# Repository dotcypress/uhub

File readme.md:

## μHub

### What is it?

μHub is USB Hub Expansion Card designed for [Clockwork uConsole](https://www.clockworkpi.com/uconsole).

### Features

* Internal Speakers Support
* 3 Type-C (USB 2.0) ports with power switch and overcurrent protection
* 1 Internal FFC (USB 2.0) port with power switch and overcurrent protection

## Resources

- [Cover Bracket 3D model](docs/cover.stl)
- [Schematics](docs/uhub.pdf)
- [PCB Viewer](https://kicanvas.org/?github=https%3A%2F%2Fgithub.com%2Fdotcypress%2Fuhub%2Fblob%2Fmain%2Fuhub.kicad_pcb)
- [Interactive BOM](https://htmlpreview.github.io/?https://github.com/dotcypress/uhub/blob/main/docs/ibom.html)

## License

Licensed under either of

- Apache License, Version 2.0 ([LICENSE-APACHE](LICENSE-APACHE) or
  http://www.apache.org/licenses/LICENSE-2.0)
- MIT license ([LICENSE-MIT](LICENSE-MIT) or http://opensource.org/licenses/MIT)

at your option.

### Contribution

Unless you explicitly state otherwise, any contribution intentionally submitted
for inclusion in the work by you, as defined in the Apache-2.0 license, shall be
dual licensed as above, without any additional terms or conditions.

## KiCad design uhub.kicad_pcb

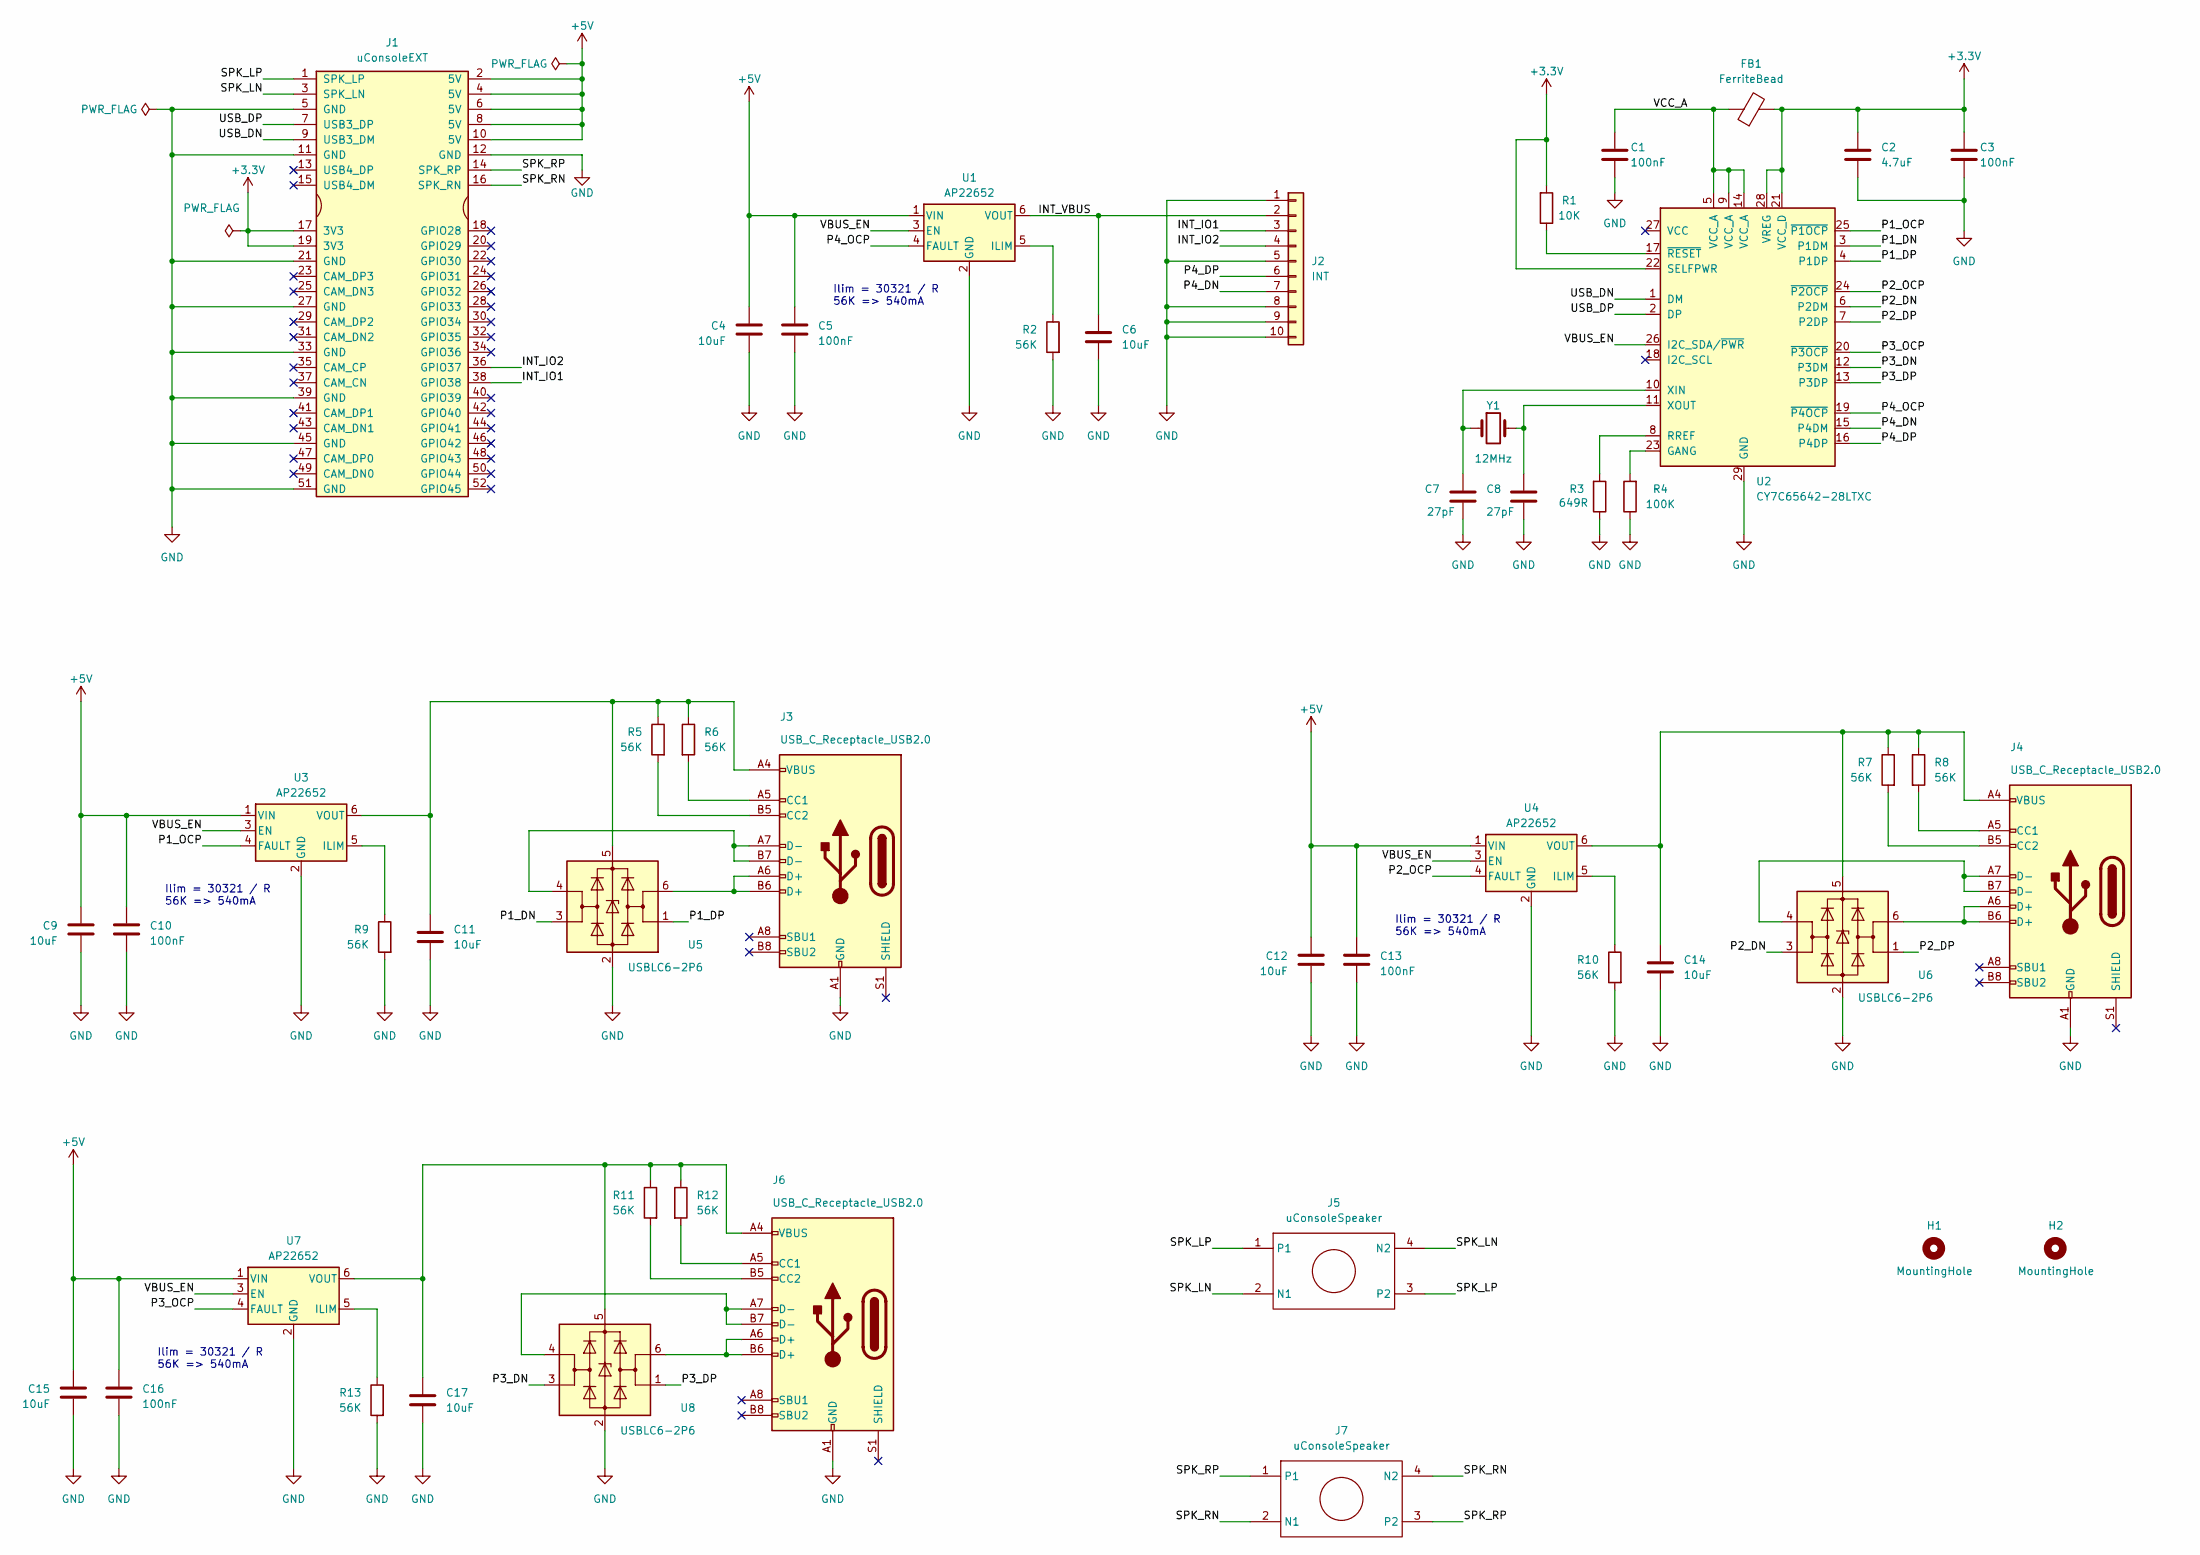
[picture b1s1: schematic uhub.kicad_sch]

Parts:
C1, C3, C5, C10, C13, C16: 100nF; C_0402_1005Metric
C2: 4.7uF; C_0402_1005Metric
C4, C6, C9, C11, C12, C14, C15, C17: 10uF; C_0603_1608Metric
C7, C8: 27pF; C_0402_1005Metric
FB1: FerriteBead; R_0603_1608Metric
H1, H2: MountingHole; MountingHole_5.3mm_M5
J1: uConsoleEXT; ext
J2: INT; Hirose_FH12-10S-0.5SH_1x10-1MP_P0.50mm_Horizontal
J3, J4, J6: USB_C_Receptacle_USB2.0; USB_C_Receptacle_HRO_TYPE-C-31-M-12
J5, J7: uConsoleSpeaker; speaker
R1: 10K; R_0402_1005Metric
R2, R5, R6, R7, R8, R9, R10, R11, R12, R13: 56K; R_0402_1005Metric
R3: 649R; R_0402_1005Metric
R4: 100K; R_0402_1005Metric
U1, U3, U4, U7: AP22652; SOT-23-6
U2: CY7C65642-28LTXC; QFN-28-1EP_5x5mm_P0.5mm_EP3.35x3.35mm
U5, U6, U8: USBLC6-2P6; SOT-666
Y1: 12MHz; Crystal_SMD_5032-2Pin_5.0x3.2mm

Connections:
+3.3V: C2.1, C3.1, FB1.2, J1.17 (3V3), J1.19 (3V3), R1.2, U2.21 (VCC_D), U2.22 (SELFPWR), U2.28 (VREG)
+5V: C4.2, C5.2, C9.2, C10.2, C12.2, C13.2, C15.2, C16.2, J1.2 (5V), J1.4 (5V), J1.6 (5V), J1.8 (5V), J1.10 (5V), U1.1 (VIN), U3.1 (VIN), U4.1 (VIN), U7.1 (VIN)
/INT_IO1: J1.38 (GPIO38), J2.3
/INT_IO2: J1.36 (GPIO37), J2.4
/INT_VBUS: C6.1, J2.2, U1.6 (VOUT)
/P1_DN: U2.3 (P1DM), U5.3 (I/O2)
/P1_DP: U2.4 (P1DP), U5.1 (I/O1)
/P1_OCP: U2.25 (~P1OCP), U3.4 (FAULT)
/P2_DN: U2.6 (P2DM), U6.3 (I/O2)
/P2_DP: U2.7 (P2DP), U6.1 (I/O1)
/P2_OCP: U2.24 (~P2OCP), U4.4 (FAULT)
/P3_DN: U2.12 (P3DM), U8.3 (I/O2)
/P3_DP: U2.13 (P3DP), U8.1 (I/O1)
/P3_OCP: U2.20 (~P3OCP), U7.4 (FAULT)
/P4_DN: J2.7, U2.15 (P4DM)
/P4_DP: J2.6, U2.16 (P4DP)
/P4_OCP: U1.4 (FAULT), U2.19 (~P4OCP)
/SPK_LN: J1.3 (SPK_LN), J5.2 (N1), J5.4 (N2)
/SPK_LP: J1.1 (SPK_LP), J5.1, J5.3 (P2)
/SPK_RN: J1.16 (SPK_RN), J7.2 (N1), J7.4 (N2)
/SPK_RP: J1.14 (SPK_RP), J7.1, J7.3 (P2)
/USB_DN: J1.9 (USB3_DM), U2.1 (DM)
/USB_DP: J1.7 (USB3_DP), U2.2 (DP)
/VBUS_EN: U1.3 (EN), U2.26 (I2C_SDA/~PWR), U3.3 (EN), U4.3 (EN), U7.3 (EN)
/VCC_A: C1.1, FB1.1, U2.5 (VCC_A), U2.9 (VCC_A), U2.14 (VCC_A)
GND: C1.2, C2.2, C3.2, C4.1, C5.1, C6.2, C7.2, C8.2, C9.1, C10.1, C11.2, C12.1, C13.1, C14.2, C15.1, C16.1, C17.2, J1.5 (GND), J1.11 (GND), J1.12 (GND), J1.21 (GND), J1.27 (GND), J1.33 (GND), J1.39 (GND), J1.45 (GND), J1.51 (GND), J2.1, J2.5, J2.8, J2.9, J2.10, J3.A1 (GND), J3.A12 (GND), J3.B1 (GND), J3.B12 (GND), J4.A1 (GND), J4.A12 (GND), J4.B1 (GND), J4.B12 (GND), J6.A1 (GND), J6.A12 (GND), J6.B1 (GND), J6.B12 (GND), R2.2, R3.1, R4.1, R9.2, R10.2, R13.2, U1.2 (GND), U2.29 (GND), U3.2 (GND), U4.2 (GND), U5.2 (GND), U6.2 (GND), U7.2 (GND), U8.2 (GND)
unnamed: J3.A5 (CC1), R6.2
unnamed: J3.B5 (CC2), R5.2
unnamed: J3.A6 (D+), J3.B6 (D+), U5.6 (I/O1)
unnamed: J3.A7 (D-), J3.B7 (D-), U5.4 (I/O2)
unnamed: J4.A5 (CC1), R8.2
unnamed: J4.B5 (CC2), R7.2
unnamed: J4.A6 (D+), J4.B6 (D+), U6.6 (I/O1)
unnamed: J4.A7 (D-), J4.B7 (D-), U6.4 (I/O2)
unnamed: J6.A5 (CC1), R12.2
unnamed: J6.B5 (CC2), R11.2
unnamed: J6.A6 (D+), J6.B6 (D+), U8.6 (I/O1)
unnamed: J6.A7 (D-), J6.B7 (D-), U8.4 (I/O2)
unnamed: R2.1, U1.5 (ILIM)
unnamed: R4.2, U2.23 (GANG)
unnamed: R3.2, U2.8 (RREF)
unnamed: C7.1, U2.10 (XIN), Y1.1
unnamed: C8.1, U2.11 (XOUT), Y1.2
unnamed: R1.1, U2.17 (~RESET)
unnamed: R9.1, U3.5 (ILIM)
unnamed: C11.1, J3.A4 (VBUS), J3.A9 (VBUS), J3.B4 (VBUS), J3.B9 (VBUS), R5.1, R6.1, U3.6 (VOUT), U5.5 (VBUS)
unnamed: R10.1, U4.5 (ILIM)
unnamed: C14.1, J4.A4 (VBUS), J4.A9 (VBUS), J4.B4 (VBUS), J4.B9 (VBUS), R7.1, R8.1, U4.6 (VOUT), U6.5 (VBUS)
unnamed: R13.1, U7.5 (ILIM)
unnamed: C17.1, J6.A4 (VBUS), J6.A9 (VBUS), J6.B4 (VBUS), J6.B9 (VBUS), R11.1, R12.1, U7.6 (VOUT), U8.5 (VBUS)

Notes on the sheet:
Ilim = 30321 / R 56K => 540mA

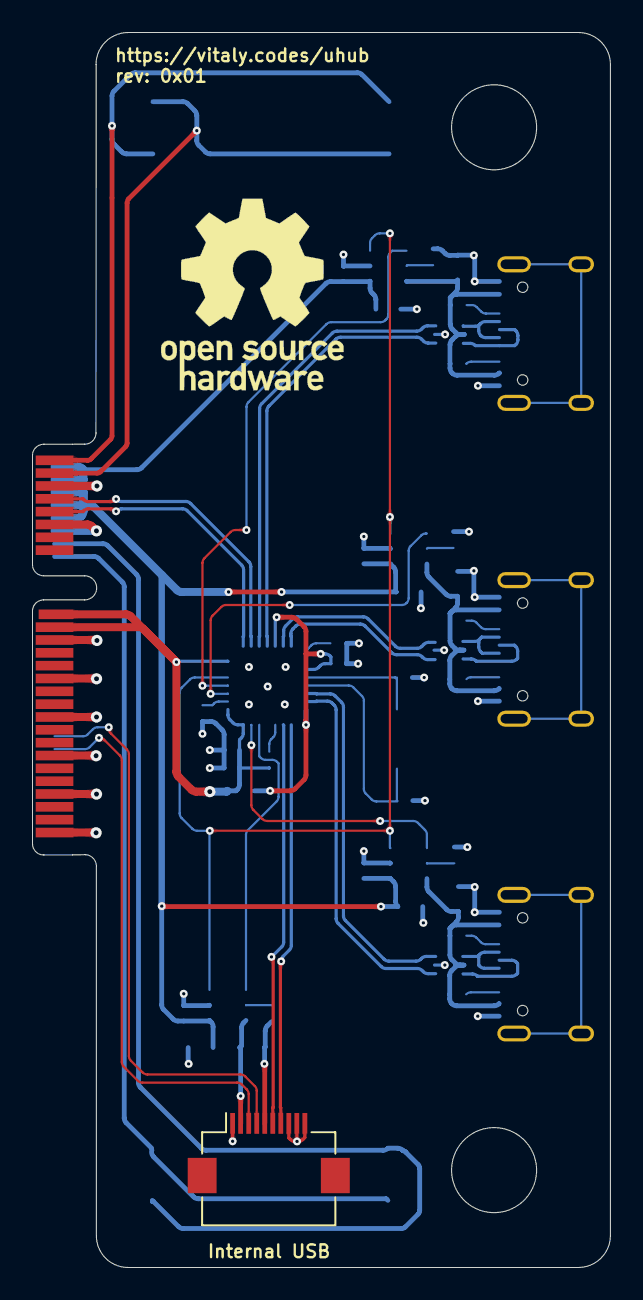
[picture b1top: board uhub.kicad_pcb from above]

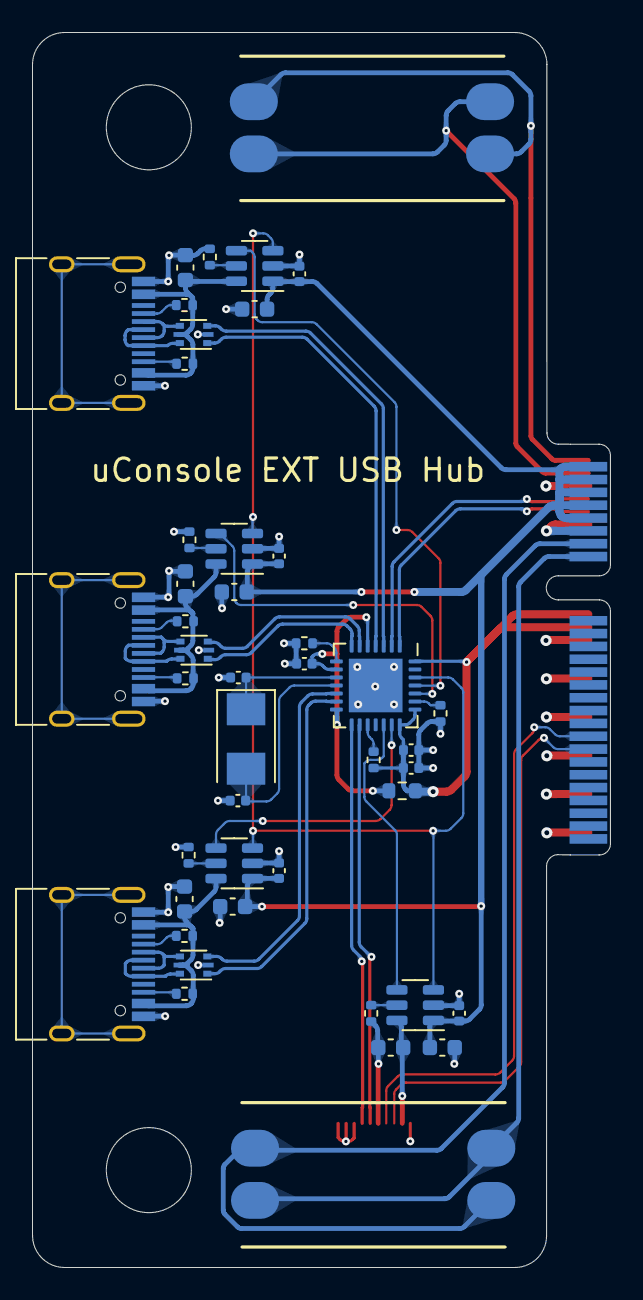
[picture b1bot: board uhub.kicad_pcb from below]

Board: 4 copper layers, 36.0 x 77.0 mm, 49 parts (45 on the bottom side), 50 nets.

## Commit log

2023-10-28 rev 0x01
2023-10-28 update cover
2023-10-31 update photo
2023-10-31 update project structure
2023-11-11 cover tuning
